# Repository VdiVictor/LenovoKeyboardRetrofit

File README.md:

# LenovoKeyboardRetrofit
KiCAD project to retrofit a kbrfbu71 keyboard from Lenovo

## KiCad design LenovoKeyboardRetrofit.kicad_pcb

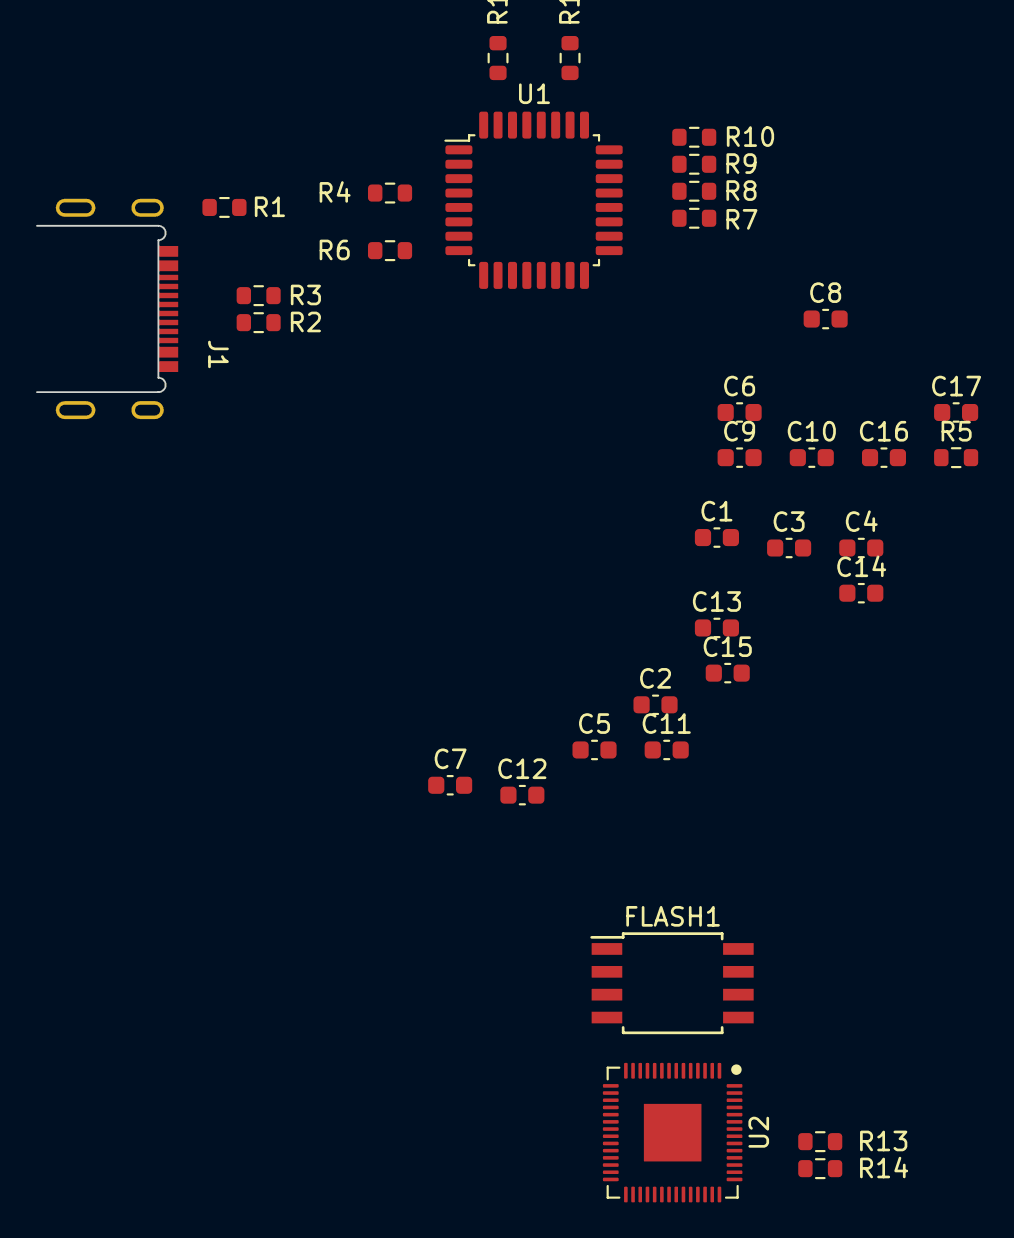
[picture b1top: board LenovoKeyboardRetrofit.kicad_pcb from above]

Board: 2 copper layers, 35 parts (0 on the bottom side), 24 nets, no tracks yet.

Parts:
C1, C3, C4, C6, C8, C9, C10, C11, C12, C13, C14, C15, C16: CAP_0603_100nF_50V; CAP_0603
C2, C5, C7, C17: CAP_0603_1uF_50V; CAP_0603
FLASH1: W25Q16JVSSIQ; SOIC-8W_5.3x5.3mm_P1.27mm
J1: USB-C_Buried; USB4510
R1, R2, R3, R13, R14: RES_0603_27R_1%; RES_0603
R4, R5, R6, R7, R8, R9, R10, R11, R12: RES_0603_10K_1%; RES_0603
U1: TUSB2036VF; LQFP-32_7x7mm_P0.8mm
U2: RP2040; QFN-56-1EP_7x7mm_P0.4mm_EP5.6x5.6mm

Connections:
+3.3V: C2.1, C3.1, C4.1, C6.1, C7.1, C8.1, C9.1, C10.1, C11.1, C12.1, C13.1, C14.1, C15.1, C16.1, C17.1, FLASH1.8 (VCC), R4.1, R7.1, R8.1, R11.1, U1.3 (VCC), U1.25 (VCC), U2.1 (IOVDD), U2.10 (IOVDD), U2.22 (IOVDD), U2.23 (DVDD), U2.33 (IOVDD), U2.42 (IOVDD), U2.43 (ADC_AVDD), U2.44 (VREG_IN), U2.45 (VREG_VOUT), U2.48 (USB_VDD), U2.49 (IOVDD), U2.50 (DVDD)
/QSPI_CLK: FLASH1.6 (CLK), U2.52 (QSPI_SCLK)
/QSPI_SD0: FLASH1.5 (DI(IO0)), U2.53 (QSPI_SD0)
/QSPI_SD1: FLASH1.2 (DO(IO1)), U2.55 (QSPI_SD1)
/QSPI_SD2: FLASH1.3 (NWP(IO2)), U2.54 (QSPI_SD2)
/QSPI_SD3: FLASH1.7 (NRST(IO3)), U2.51 (QSPI_SD3)
/QSPI_SS: FLASH1.1 (SS), U2.56 (QSPI_SS)
/TUSB_~RST: C1.1, R4.2, U1.4 (~RST)
/US_USB_DN: J1.A7 (DN1), J1.B7 (DN2), R3.1
/US_USB_DP: J1.A6 (DP1), J1.B6 (DP2), R2.1
unnamed: C10.2, C11.2, C12.2, C13.2, C14.2, C15.2, C16.2, C17.2
unnamed: J1.0, R1.2
unnamed: J1.A4/B9 (VBUS), J1.A9/B4 (VBUS)
unnamed: R5.2, U1.6 (EEDATA/~GANGED)
unnamed: R6.2, U1.8 (~BUSPWR)
unnamed: R7.2, U1.21 (~OCPROT/~PWRSW)
unnamed: R8.2, U1.22 (NPINT0)
unnamed: R9.2, U1.23 (NPINT1)
unnamed: R10.2, U1.24 (~NP3)
unnamed: R11.2, U1.26 (~EXTMEM)
unnamed: R12.2, U1.31 (MODE)
unnamed: R13.1, U2.47 (USB_DP)
unnamed: R14.1, U2.46 (USB_DM)
VSS: C1.2, C2.2, C3.2, C4.2, C6.2, C7.2, C8.2, C9.2, FLASH1.4 (GND), J1.A1/B12 (GND), J1.A12/B1 (GND), R1.1, R5.1, R6.1, R9.1, R10.1, R12.1, U1.7 (GND), U1.28 (GND), U2.19 (TESTEN), U2.57 (GND)

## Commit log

2022-03-19 Gitignore
2022-03-19 Modification of sch
2022-03-20 Adding of TUSB usb hub
2022-03-21 First config of TUSB
2022-03-21 USB connectors
